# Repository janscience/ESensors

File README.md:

# ESensors

A library for environmental sensors (air and water) for Teensy and
Arduino with additional background information.

## [ESensors](https://github.com/janscience/ESensors) library

### Features

- Blocking and non-blocking reads from many sensors in parallel.
- Sensor readings in adaptable units.
- Output of sensor properties and readings on streams and into CSV files on SD card.
- Hardware independent derived measures, like for example, dew point and absolute humidity.
- Device properties and settings available as metadata.

### Currently supported sensors

- VoltageADC: voltage
- [BH1750](docs/chips/bh1750.md): [light intensity](docs/parameters/light.md)
- [BME280](docs/chips/bme280.md): [air pressure](docs/parameters/airpressure.md), [temperature](docs/parameters/temperature.md), and [humidity](docs/parameters/humidity.md)
- [DS18x20](docs/chips/ds18x20.md): [temperature](docs/parameters/temperature.md)
- [DS3231](docs/chips/ds3231.md): [temperature](docs/parameters/temperature.md)
- [TSL2591](docs/chips/tsl2591.md): [light intensity](docs/parameters/light.md)
- [DHT](docs/chips/dht.md): [temperature](docs/parameters/temperature.md)
- [STS4x](docs/chips/sts4x.md): [temperature](docs/parameters/temperature.md)

### Documentation

- [Installation instructions](docs/install.md)
- [User guide](docs/userguide.md)
- [Class overview](docs/classes.md)
- [Sensor chips](docs/chips/): Infos on development boards and libraries for
  specific sensor chips.

## Environmental parameters

- [Parameters](docs/parameters/): Infos on principles, methods, and
  available chips for measuring various environmental parameters.

## Examples

In [examples/](examples) you find sketches demonstrating the use of
the ESensors library.

- [sensors](examples/sensors): read sensors and write readings to serial.
- [logger](examples/logger): periodically write sensor readings with time stamp into a CSV file.
- [snoozelogger](examples/snoozelogger): same as [logger example](examples/logger), but with hibernate between sensor readings.

## Utilities

In [utils/](utils) you find useful python scripts.

- [sensors.py](utils/sensors.py): plot the content of the csv file written by the [ESensors](doc/classes.md#esensors) library.
- [fixsensortimestamps.py](utils/fixsensortimestamps.py): Fix sensor time stamps.

## Circuit boards

Inside the `pcbs/` folder you find circuit boards using various
environmental sensors.

- [Sensors-V1](pcbs/sensorsv1/): temperature and light sensor with status LEDs.

## Power supply

- [Power supply](docs/power/): some solutions for power supply.

## TODO

- Add more sensors.

## Applications of the ESensors library

ESensors is used in:

- [EOD-Logger](https://github.com/janscience/EOD-Logger): A 2-electrode
  logger for recording electric-organ discharges of electric fish.

- [TeeGrid](https://github.com/janscience/TeeGrid): Electrode arrays
  based on 8-16channel recording devices for recording electric fish
  behavior in natural habitats (see [Henninger et
  al. 2018](https://doi.org/10.1523/JNEUROSCI.0350-18.2018) and
  [Henninger et al. 2020](https://doi.org/10.1242/jeb.206342)).

- [FishFinder](https://github.com/janscience/FishFinder): A
  replacement for the usual and horrible RadioShack/MP3 player
  combination for recording electric fish EODs in their natural
  habitats with lot's of additional features (display, online
  analysis, acoustic feedabck, environmental parameters).

## Links

- [SmartRock](https://github.com/OPEnSLab-OSU/SmartRock/wiki) from the
  [OPenSLab](https://open-sensing.org/) at Oregon-State University.

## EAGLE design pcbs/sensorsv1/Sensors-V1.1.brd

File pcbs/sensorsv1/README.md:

# Senors V1

Temperature and light sensor with status LEDs.

Based on

- [BH1750 or BH1730](../../docs/chips/bh1750.md) ambient light sensor
- [Sensirion STS40](../../docs/chips/sts4x.md) temperature sensor
- [PCA9536](pca9536.pdf) 4-bit I2C-bus I/O port for driving status LEDs

by [jlm Innovation](https://www.jlm-innovation.de/) and [Jan
Benda](https://github.com/janscience).

## Circuit

### Version 1.1

(smaller pads and 0.5mm less wide)

- [EAGLE schematics file](Sensors-V1.1.sch)
- [EAGLE circuit board](Sensors-V1.1.brd)

### Version 1

- [EAGLE schematics file](Sensors-V1.sch)
- [EAGLE circuit board](Sensors-V1.brd)

### Version 2

Since the BH1750 is not produced anymore, we need to select another
light sensor which supports at least two I2C addresses.
For example, the TI OPT3001 ambient light sensor.

## LEDs

- [LITE-ON 639nm](LTST_C190KRKT-1141828.pdf): SMD, red
- [LITE-ON 468nm](LTST_C193TBKT_5A-1175300.pdf): SMD, blue
- [OSRAM 850nm](sfh4555.pdf): through-hole, infrared

## Code

- [ESensors/LightBH1750.h](../../src/LightBH1750.py)
- [ESensors/TemperatureSTS4x.h](../../src/TemperatureSTS4x.h)
- [TeeRec/DigitalIOPCA9536.h](https://github.com/janscience/TeeRec/blob/main/src/DigitalIOPCA9536.h)

```cpp
#include <Wire.h>
#include <SDCard.h>
#include <Blink.h>
#include <ESensors.h>
#include <TemperatureSTS4x.h>
#include <LightBH1750.h>
#include <DigitalIOPCA9536.h>

#define STS4x_ADDR  STS4x_ADDR2   // I2C address of STS4x temperature sensor

ESensors sensors;
TemperatureSTS4x tempsts(&sensors);
LightBH1750 light1(&sensors);
LightBH1750 light2(&sensors);

DigitalIOPCA9536 gpio;
Blink blink("status", LED_BUILTIN);
Blink errorblink("error");
Blink syncblink("sync");

SDCard sdcard;

void setup() {
  sdcard.begin();
  Wire2.begin();
  gpio.begin(Wire2);
  blink.setPin(gpio, 0);
  errorblink.setPin(gpio, 1);
  syncblink.setPin(gpio, 3);
  blink.switchOff();
  errorblink.switchOff();
  syncblink.switchOff();
  gpio.setMode(2, INPUT);
  light1.begin(Wire2, BH1750_TO_GROUND);
  light1.setQuality(BH1750_QUALITY_HIGH2);
  light1.setName("illuminance1");
  light1.setSymbol("I1");
  light2.begin(Wire2, BH1750_TO_VCC);
  light2.setQuality(BH1750_QUALITY_HIGH2);
  light2.setName("illuminance2");
  light2.setSymbol("I2");
  tempsts.begin(Wire2, STS4x_ADDR);
  tempsts.setPrecision(STS4x_HIGH);
  sensors.setPrintTime(ESensors::NO_TIME);
  sensors.start();
  sensors.setInterval(10.0);
  sensors.setPrintTime(ESensors::ISO_TIME);
  sensors.reportDevices();
  sensors.report();
  sensors.start();
  sensors.read();
  sensors.start();
  sensors.read();
  sensors.openCSV(sdcard, "sensors.csv");
}

void loop() {
  if (sensors.update(blink.isOn() || syncblink.isOn())) {
    sensors.writeCSV();
    sensors.print(true, true);
  }
}
```

## Applications

- [R5-logger](https://github.com/janscience/TeeGrid/tree/main/examples/R5-logger) 
- [R4-sensors-logger](https://github.com/janscience/TeeGrid/tree/main/examples/R4-sensors-logger)

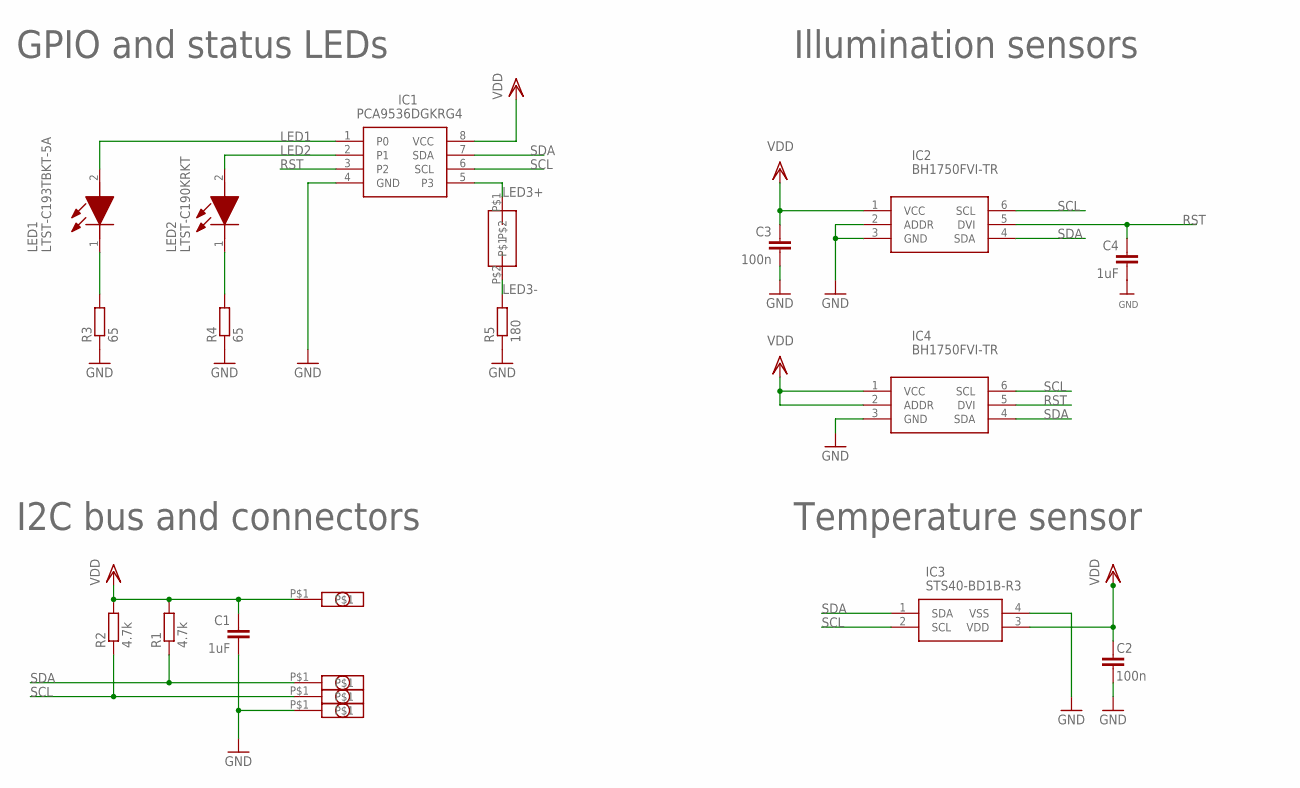
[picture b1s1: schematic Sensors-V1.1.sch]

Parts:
C1, C4: 1uF; C0603
C2, C3: 100n; C0603
IC1: PCA9536DGKRG4; SOP65P490X110-8N
IC2, IC4: BH1750FVI-TR; WSOF6
IC3: STS40-BD1B-R3; STS40BD1BR3
LED1: LTST-C193TBKT-5A; LEDC1608X45N
LED2: LTST-C190KRKT; LEDC1607X80N
R1, R2: 4.7k; R0603
R3, R4: 65; R0603
R5: 180; R0603
U$1, U$2, U$3, U$4: PADL8; PAD-8
U$5: LEDPINS; LEDPINS254

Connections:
GND: C1.2, C2.2, C3.2, C4.2, IC1.4 (GND), IC2.2 (ADDR), IC2.3 (GND), IC3.4 (VSS), IC4.3 (GND), R3.1, R4.1, R5.1, U$3.P$1
LED1: IC1.1 (P0), LED1.2 (A)
LED2: IC1.2 (P1), LED2.2 (A)
LED3+: IC1.5 (P3), U$5.P$1
LED3-: R5.2, U$5.P$2
unnamed: LED1.1 (K), R3.2
unnamed: LED2.1 (K), R4.2
RST: C4.1, IC1.3 (P2), IC2.5 (DVI), IC4.5 (DVI)
SCL: IC1.6 (SCL), IC2.6 (SCL), IC3.2 (SCL), IC4.6 (SCL), R2.1, U$2.P$1
SDA: IC1.7 (SDA), IC2.4 (SDA), IC3.1 (SDA), IC4.4 (SDA), R1.1, U$1.P$1
VDD: C1.1, C2.1, C3.1, IC1.8 (VCC), IC2.1 (VCC), IC3.3 (VDD), IC4.1 (VCC), IC4.2 (ADDR), R1.2, R2.2, U$4.P$1

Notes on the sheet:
Temperature sensor
Illumination sensors
GPIO and status LEDs
I2C bus and connectors

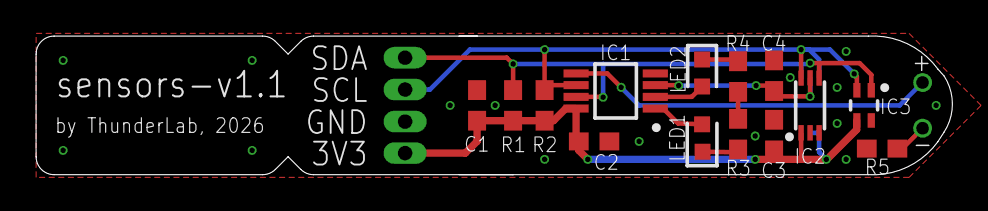
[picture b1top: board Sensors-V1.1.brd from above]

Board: 2 copper layers, 50.9 x 7.7 mm, 20 parts (1 on the bottom side), 11 nets.

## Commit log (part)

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2022-04-16 README on conductivity
2022-04-16 added foundries link
2022-04-16 added water velocity
2022-04-16 fixed EC
2022-04-16 note on AC frequency
2022-04-16 added hardware sources
2022-04-17 added turbitity
2022-04-17 added rain
2022-04-18 added water level
2022-04-19 improved equations
2022-04-19 degrees celsius
2022-04-20 added light
2022-04-21 added air pressure
2022-04-21 added air pressure hardware and pinputs
2022-04-21 commented pressure libraries
2022-04-21 structures pressure libraries
2022-04-21 added power supply
2022-04-21 wiring info for Adafruit backpack
2022-04-21 cutting info for Adafruit backpack
2022-04-21 added notes to bme280 code examples
2022-04-22 soft power switch
2022-04-22 charger LEDs
2022-04-22 update on bme280 libraries
2022-04-22 few more notes
2022-04-22 added temperature and humidity
2022-04-22 fixed file name
2022-04-22 updated .gitignore
2022-04-24 moved sensor library from TeeRec here
2022-04-24 added library.properties
2022-04-24 [Sensor] fixed inheritance from SensorDevice
2022-04-24 [SenseBME280] inherits from SensorDevice
2022-04-25 fixed example sketches
2022-04-25 [Sensors] fixed path for open file
2022-04-25 renamed doc/ to docs/
2022-04-25 restructured documentation
2022-04-25 [docs] fixed relative links
2022-04-25 [docs] added tsl2591
2022-04-25 [docs] tsl2591 library survey
2022-04-25 [LightTSL2591] first working implementation
2022-04-26 [light] notes on units
2022-04-26 [LightTSL2591] adapted to alternative bus interface
2022-04-26 [LightTSL2591] added sensor id
2022-04-26 [LightTSL2591] added temperature correction and raw values
2022-04-26 [LightTSL2591] variable delay
2022-04-27 renamed read() and readData() to get() and getData()
2022-04-27 added blocking read() function
2022-04-27 [examples] new tsl2591calibration
2022-04-27 [examples] fixed tsl2591calibration
2022-04-27 [docs] forum discussion to irradiance and lux
2022-04-27 [TSL2591] explanation of irradiance calibration
2022-04-27 [LightTSL2591] added IR factor
2022-04-28 [LightTSL2591] changed IR factor to IR ratio
2022-04-28 [TSL2591] added description of lux equation
2022-04-28 [TSL2591] fixed links
2022-04-28 [TSL2591] small fixes
2022-04-28 [LightTSL2591] addedd illumination
2022-04-28 [Sensors] flexible output of time stamps
2022-04-28 [LightTSL2591] auto gain
2022-04-28 [logger] added LightTSL2591
2022-04-29 [docs] fixed text and scaled images
2022-04-29 [docs] fixed scaled images
2022-04-29 [senors] names without units
2022-04-30 passes arduino-lint
2022-04-30 renamed repo to Sensors
2022-04-30 added links to various advanced water sensors
2022-04-30 [docs] added bh1750
2022-04-30 delay() is now delayTime()
2022-04-30 simplified resolution interface
2022-04-30 simplified chip and identifier interface
2022-04-30 new SensorValue template class
2022-04-30 new snoozelogger example
2022-04-30 updated README for new classes and example
2022-04-30 removed TeeRec dependencies of examples
2022-05-01 [docs] comment on power banks shutting off
2022-05-01 [LightTSL2951] illuminance is extra Sensor
2022-05-01 [SensorDevice] virtual chip() and indetifier()
2022-05-01 added TSL2591MI to dependencies
2022-05-01 [Sensor] SI unit prefixes
2022-05-01 [sensors] improved for serial plotter
2022-05-02 [Sensor] general setSIPrefix() function
2022-05-02 [docs] library survey bh1750
2022-05-02 [Sensor] improved format parsing and modification
2022-05-02 [SensorDerived] new base calss for derived sensr readings
2022-05-03 [DewPoint] general dew point computation
2022-05-03 [AbsoluteHumidity] general computation of absolute humidity
2022-05-03 [SeaLevelPressure] general computation of sea level pressure
2022-05-03 [docs] improved humidity and pressure
2022-05-03 [docs] extra installation instructions
2022-05-03 [docs] new user guide
2022-05-04 [docs] added note on setInterval()
2022-05-04 [docs] this is C++ code, not python!
2022-05-06 [docs] units and csv file for usage.md
2022-05-06 [docs] fixes
2022-05-06 [Sensors] dynamic delayTime()
2022-05-06 [Sensors] pending() is now pendingCSV
2022-05-06 [doc] added to user guide
2022-05-07 [doc] all classes of the LightTSL header
2022-05-07 [doc] all classes of the SenseBME280 header
2022-05-07 [doc] clas structure
2022-05-07 [doc] finished class structure
2022-05-07 [Sensors] added timeStamp()
2022-05-07 [docs] updated links
2022-05-07 changed name to ESensors
2022-05-07 [docs] updated library criteria
2022-05-07 [github/workflows] added arduino lint
2022-05-07 [github/workflows] added badge
2022-05-07 [github/workflows] renamed to arduino-lint
2022-05-07 [github/workflows] fixed badge
2022-05-07 [docs] TOC for user guide
2022-05-07 [DerivedESensor] improved chip and identifier assembly
2022-05-07 humidity as fraction and fixed derived humidity measures
2022-05-08 improved equation for dew point
2022-05-08 [docs] svg equations
2022-05-08 [paramters] no more subdirectories
2022-05-09 [docs] updated link to capacitive rain sensor
2022-05-09 [utils] support units with slash
2022-05-09 [workflows] changed arduino-lint to update
2022-05-10 updated installation instructions
2022-05-10 [docs] added miniDOT link
2022-05-10 more detailed description
2022-05-10 [docs] library survey for dallas temperature
2022-05-10 [docs] added ds18x20.md
2022-05-10 [docs] link to ds18x20 from temperature page
2022-05-11 [LightTSL2591] better format for illuminance
2022-05-11 [examples] temperature correction for logger
2022-05-11 [docs] added feature list
2022-05-12 [docs] added csv file to docs
2022-05-12 [ESensor] compact format, valueStr() and resolutionStr()
2022-05-13 [conductivity] added equations for the voltage divider
2022-05-13 [conductivity] fixed Ohm
2022-05-13 [conductivity] fixed italics
2022-05-13 [conductivity] fixed spelling
2022-05-13 [conductivity] first example sketch
2022-05-14 [ESensors] more optional compact outputs
2022-05-14 [conductivity] use non blocking ADC interface
2022-05-15 [conductivity] ESensor classes for voltage readings
2022-05-15 more specific architecture for library.properties
2022-05-17 [conductivity] calibration
2022-05-17 [conductivity] calibration fixes
2022-05-18 [conductivity] fixes
2022-05-18 Teensyduino spelling
2022-05-30 [docs] library survey for BH1750
2022-05-30 [LightBH1750] new ESensor for BH1750
2022-05-31 [LightBH1750] variable delayTime()
2022-06-05 [bh1750] added images
2022-06-05 [bh1750] cropped images
2022-06-05 [LightBH1750] added setQuality() and setIntegrationTime()
2022-06-05 [LightBH1750] added raw, quality and mtreg outputs
2022-06-05 [ESensors] fixed dynamic delay times
2022-06-07 updated examples
2022-06-12 [docs] improved chip documentation
2022-06-12 [docs] updated class documentation
2022-06-28 added hp_BH1750 library files
2022-07-05 version 1.1.0
2022-07-13 added TODO
2023-01-17 added new folder on housings
2023-07-24 fixed docu
2023-07-24 added DHT docu
2023-07-24 new SenseDHT class
2023-07-25 added retrieve() functions for continued communication
2023-10-09 better pin name
2023-11-17 added SmartRock link
2024-06-14 [docs] updated installation instructions
2024-08-08 [SenseDHT] commented all DHT code to remove dependency
2024-08-08 [install] updated installation instructions
2024-08-10 [ESensors] improved serial output
2024-08-12 [ESensors] fixed oneline print
2024-09-10 [doc] added links to vaious chips and projects
2024-10-01 [temperature] added accuracy
2024-12-28 Optional stream argument instead of Serial
2024-12-28 [ESensorDevice] added bus and address information
2024-12-28 [doc] update and fixes
2025-01-04 [ESensorDevice] enumerate I2C and SPI bus, improved report
2025-01-05 [ESensor] add access to underlying ESensorDevice
2025-01-05 [ESensors] report() and reportDevices() working
2025-01-06 [ESensorDevice] fixes
2025-01-10 [ESensorDevice] address without leading zeros
2025-01-10 prepare for next release
2025-01-11 [ESensors] fixed print() without time stamp
2025-01-11 [ESensors] fixed print() not available sensor
2025-01-11 [ESensors] fixed print() no output for not available sensors
2025-01-11 [ESensors] delayTime isi n millisencods
2025-01-11 [ESensors] fixed print for unavailable sensors
2025-01-13 [SenseDHT] works
2025-01-13 [ESensorDevice] removed retrieve() mechanism
2025-01-13 [docs] updated output of report() and print()
2025-01-13 prepare for v1.4.0 release
2025-01-18 [TemperatureDS3231] reads temperature of real-time clock
2025-07-01 [temperature] added small chips
2025-07-03 [utils] started fixsensortimestamps.py
2025-07-03 [fixtimestamps] working
2025-07-14 fixed links
2025-07-14 [bh1750] fixed links
2025-07-14 [bh1750] fixed image width
2025-07-20 added some data sheets
2025-08-23 [LightBH1750] improved docu
2025-08-23 [STS4x] added infos to Sensirion STS4x chips
2025-08-23 [STS4x] full implementation
2025-08-23 [STS4x] updated documentation
2025-08-23 [sensors] I2C address for light sensor
2025-08-23 [ESensors] added buffer time and isBusy()
2025-08-23 [ESensors] retrieve sensor readings only if allowed
2025-08-31 prepare v1.5.0
2025-10-20 [sensorsv1] added pcbs
2025-11-06 [ESensorsDevice] added metadata infrastructire
2025-11-07 set metadata in all sensors
2025-11-07 [ESensorDevice] write meta data
2025-11-07 [ESensorDevice] fixed string termination
2025-11-20 [waterlevel] use math markdown
2025-11-20 [waterlevel] fixed math markdown
2026-03-27 [VoltageADC] new ESensor for reading voltages from internal ADC
2026-03-27 [ESensors] add file extension if not already present
2026-03-28 [ESensor] expanded interface for setting conversionfactor and offset
2026-03-30 [VoltageADC] improved metadata
2026-05-06 version 1.6.0
2026-05-28 added BH1730 data sheet

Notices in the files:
parts and their libraries:
microbuilder: This work is placed in the public domain, and may be freely used for commercial and non-commercial work with the following conditions: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
